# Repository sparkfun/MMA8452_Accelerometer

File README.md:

SparkFun Triple Axis Accelerometer Breakout - MMA8452Q
=============================================

<table class="table table-hover table-striped table-bordered">
  <tr align="center">
   <td></td>
   <td></td>
  </tr>
  <tr align="center">
    <td>SparkFun Triple Axis Accelerometer Breakout - MMA8452Q [<a href="https://www.sparkfun.com/products/12756">SEN-12756</a>]</td>
    <td>SparkFun Triple Axis Accelerometer Breakout - MMA8452Q (with Headers)
[<a href="https://www.sparkfun.com/products/13926">BOB-13926</a>]</td>
  </tr>
</table>

This breakout board makes it easy to use the tiny MMA8452Q accelerometer in your project. 
The MMA8452Q is a smart low-power, three-axis, capacitive micro-machined accelerometer with 12 bits of resolution.

Repository Contents
-------------------
* **/Firmware** - Example Arduino sketches for interfacing with the accelerometer
* **/Hardware** - All Eagle design files (.brd, .sch)
* **/Libraries** - Libraries for use with the accelerometer
* **/Production** - Production panel files (.brd)

Documentation
--------------
* Library
  * **[Arduino Library](https://github.com/sparkfun/SparkFun_MMA8452Q_Arduino_Library)** - Arduino library for the accelerometer.
  * **[Particle Library](https://github.com/sparkfun/SparkFun_MMA8452Q_Particle_Library)** - Particle library for the accelerometer.
* **[Hookup Guide](https://learn.sparkfun.com/tutorials/mma8452q-accelerometer-breakout-hookup-guide)** - Basic hookup guide for the accelerometer.
* **[SparkFun Fritzing repo](https://github.com/sparkfun/Fritzing_Parts)** - Fritzing diagrams for SparkFun products.
* **[SparkFun 3D Model repo](https://github.com/sparkfun/3D_Models)** - 3D models of SparkFun products. 

Product Versions
----------------
* [BOB-13926](https://www.sparkfun.com/products/13926) - Version 11 with headers
* [SEN-12756](https://www.sparkfun.com/products/12756) - Version 11
* *[SEN-10955 (Retired)](https://www.sparkfun.com/products/retired/10955)* - Version 11

License Information
-------------------
This product is _**open source**_! 

The **hardware** is released under [Creative Commons ShareAlike 4.0 International](https://creativecommons.org/licenses/by-sa/4.0/).

The **code** is beerware; if you see me (or any other SparkFun employee) at the local, and you've found our code helpful, please buy us a round!

Please use, reuse, and modify these files as you see fit. Please maintain attribution to SparkFun Electronics and release anything derivative under the same license.

Distributed as-is; no warranty is given.

- Your friends at SparkFun.

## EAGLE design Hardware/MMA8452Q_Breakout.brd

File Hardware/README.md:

SparkFun <PRODUCT NAME> Design Files
=====================================

The .sch and .brd files hare are Eagle CAD schematic and PCB design files from SparkFun Electronics.
A freeware version of Eagle can be found [here](http://www.cadsoftusa.com/download-eagle/freeware/). 

License
---------
This product is open source! 
The hardware is released under [Creative Commons ShareAlike 4.0 International](https://creativecommons.org/licenses/by-sa/4.0/).

Please use, reuse, and modify these files as you see fit. Please maintain attribution to SparkFun Electronics and release anything derivative under the same license.

Distributed as-is; no warranty is given.

- Your friends at SparkFun.

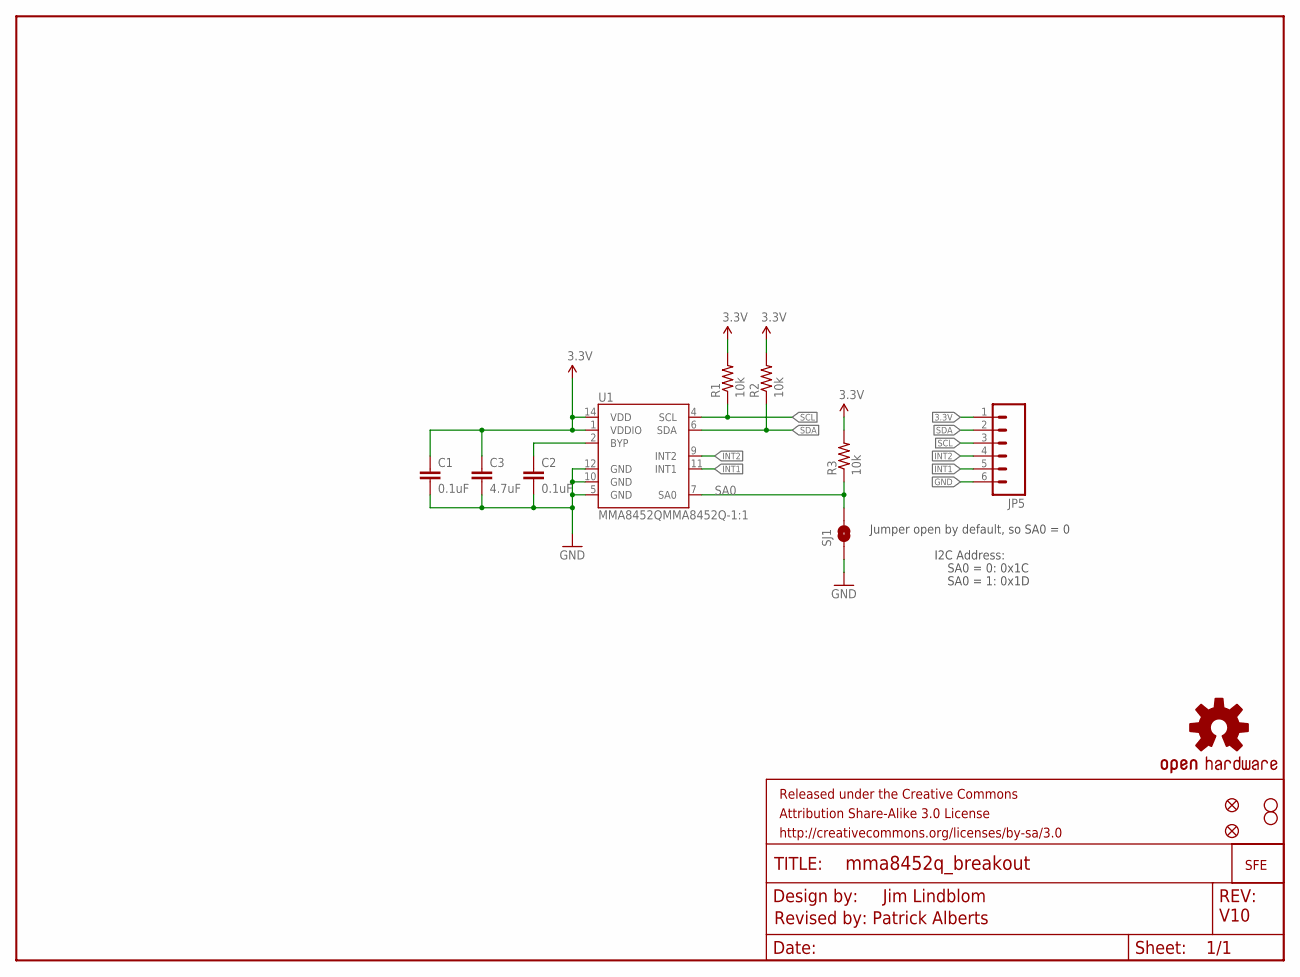
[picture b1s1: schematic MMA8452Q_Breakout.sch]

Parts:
C1, C2: 0.1uF; 0603-CAP
C3: 4.7uF; 0603-CAP
FID1, FID2: FIDUCIAL1X2; FIDUCIAL-1X2
FRAME1: FRAME-LETTER; CREATIVE_COMMONS
JP1: LOGO-SFESK; SFE-LOGO-FLAME
JP3, JP4: STAND-OFF
JP5: M06SIP; 1X06
R1, R2, R3: 10k; 0603-RES
SJ1: SOLDERJUMPERNO; SJ_2S-NO
U1: MMA8452QMMA8452Q-1:1; MMA8452Q-1:1
U$1: OSHW-LOGOS; OSHW-LOGO-S

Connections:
3.3V: C1.1, C3.1, JP5.1, R1.2, R2.2, R3.2, U1.1 (VDDIO), U1.14 (VDD)
BYP: C2.1, U1.2 (BYP)
GND: C1.2, C2.2, C3.2, JP5.6, SJ1.1, U1.5 (GND), U1.10 (GND), U1.12 (GND)
INT1: JP5.5, U1.11 (INT1)
INT2: JP5.4, U1.9 (INT2)
SA0: R3.1, SJ1.2, U1.7 (SA0)
SCL: JP5.3, R1.1, U1.4 (SCL)
SDA: JP5.2, R2.1, U1.6 (SDA)

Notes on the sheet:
Jim Lindblom
I2C Address:
SA0 = 0: 0x1C
SA0 = 1: 0x1D
Jumper open by default, so SA0 = 0
Revised by: Patrick Alberts
V10

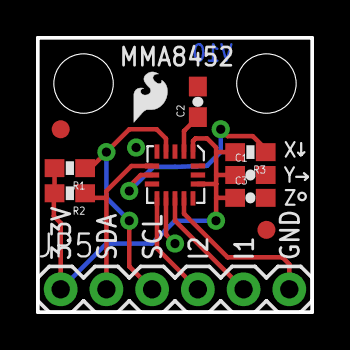
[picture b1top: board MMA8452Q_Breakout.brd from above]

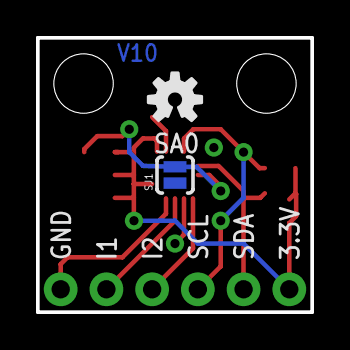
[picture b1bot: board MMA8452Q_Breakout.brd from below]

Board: 2 copper layers, 15.2 x 15.2 mm, 16 parts (2 on the bottom side), 8 nets.

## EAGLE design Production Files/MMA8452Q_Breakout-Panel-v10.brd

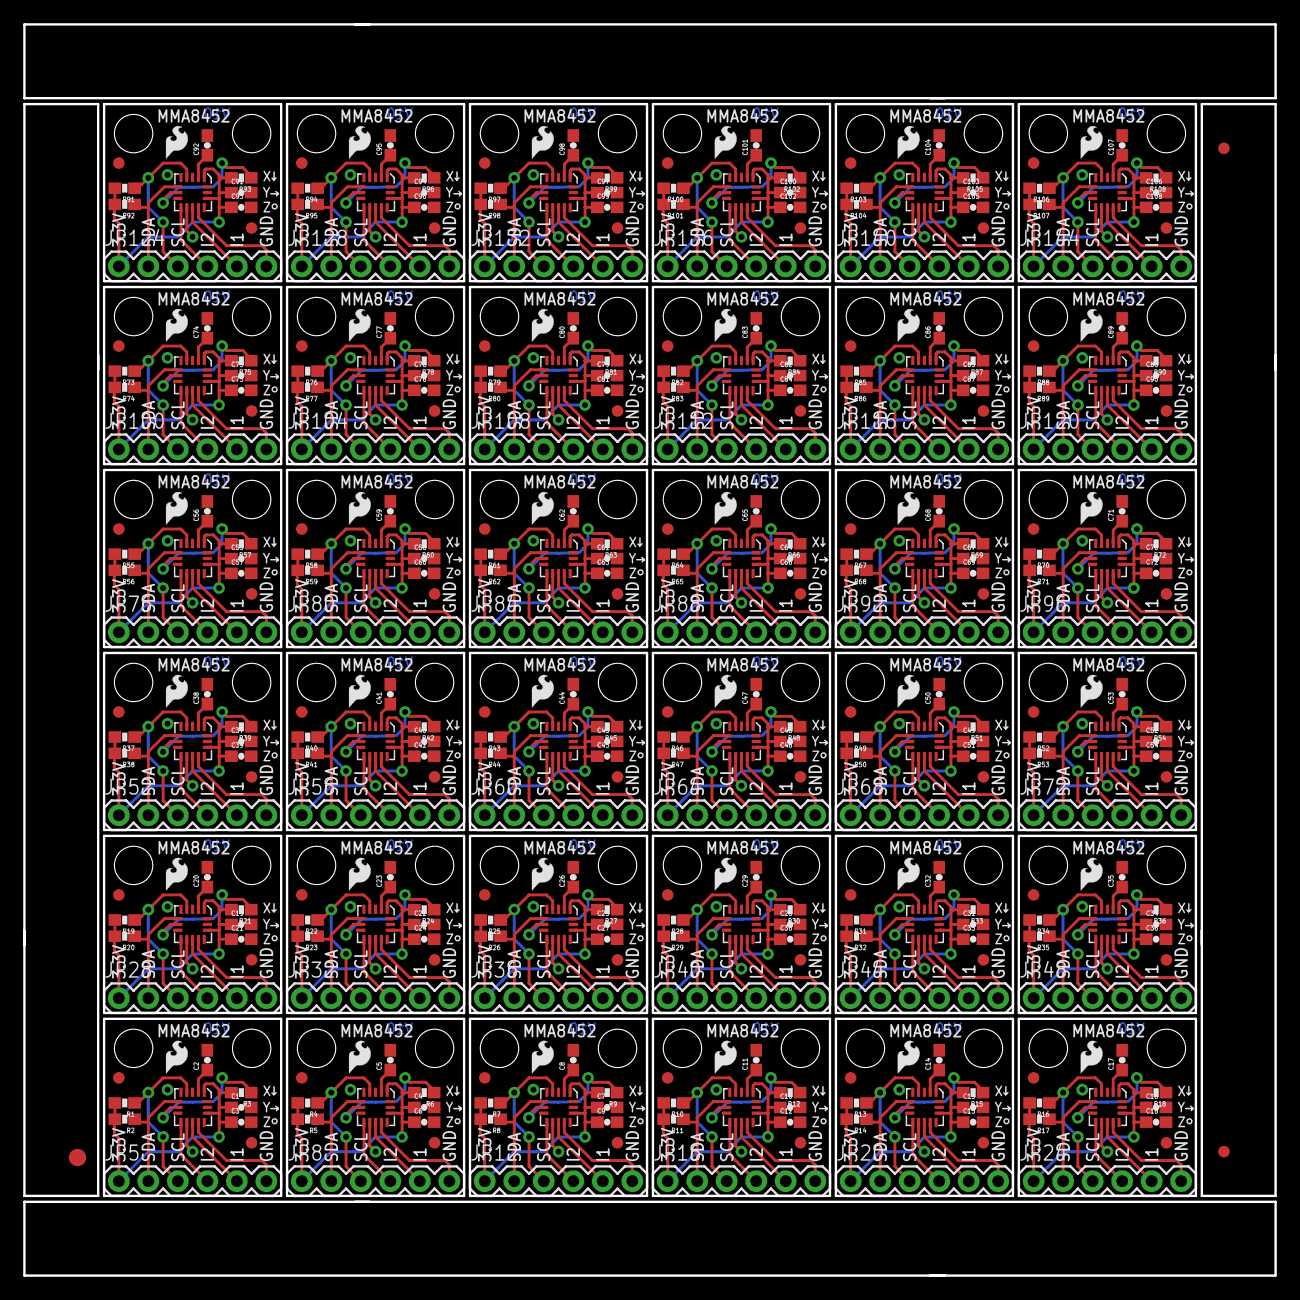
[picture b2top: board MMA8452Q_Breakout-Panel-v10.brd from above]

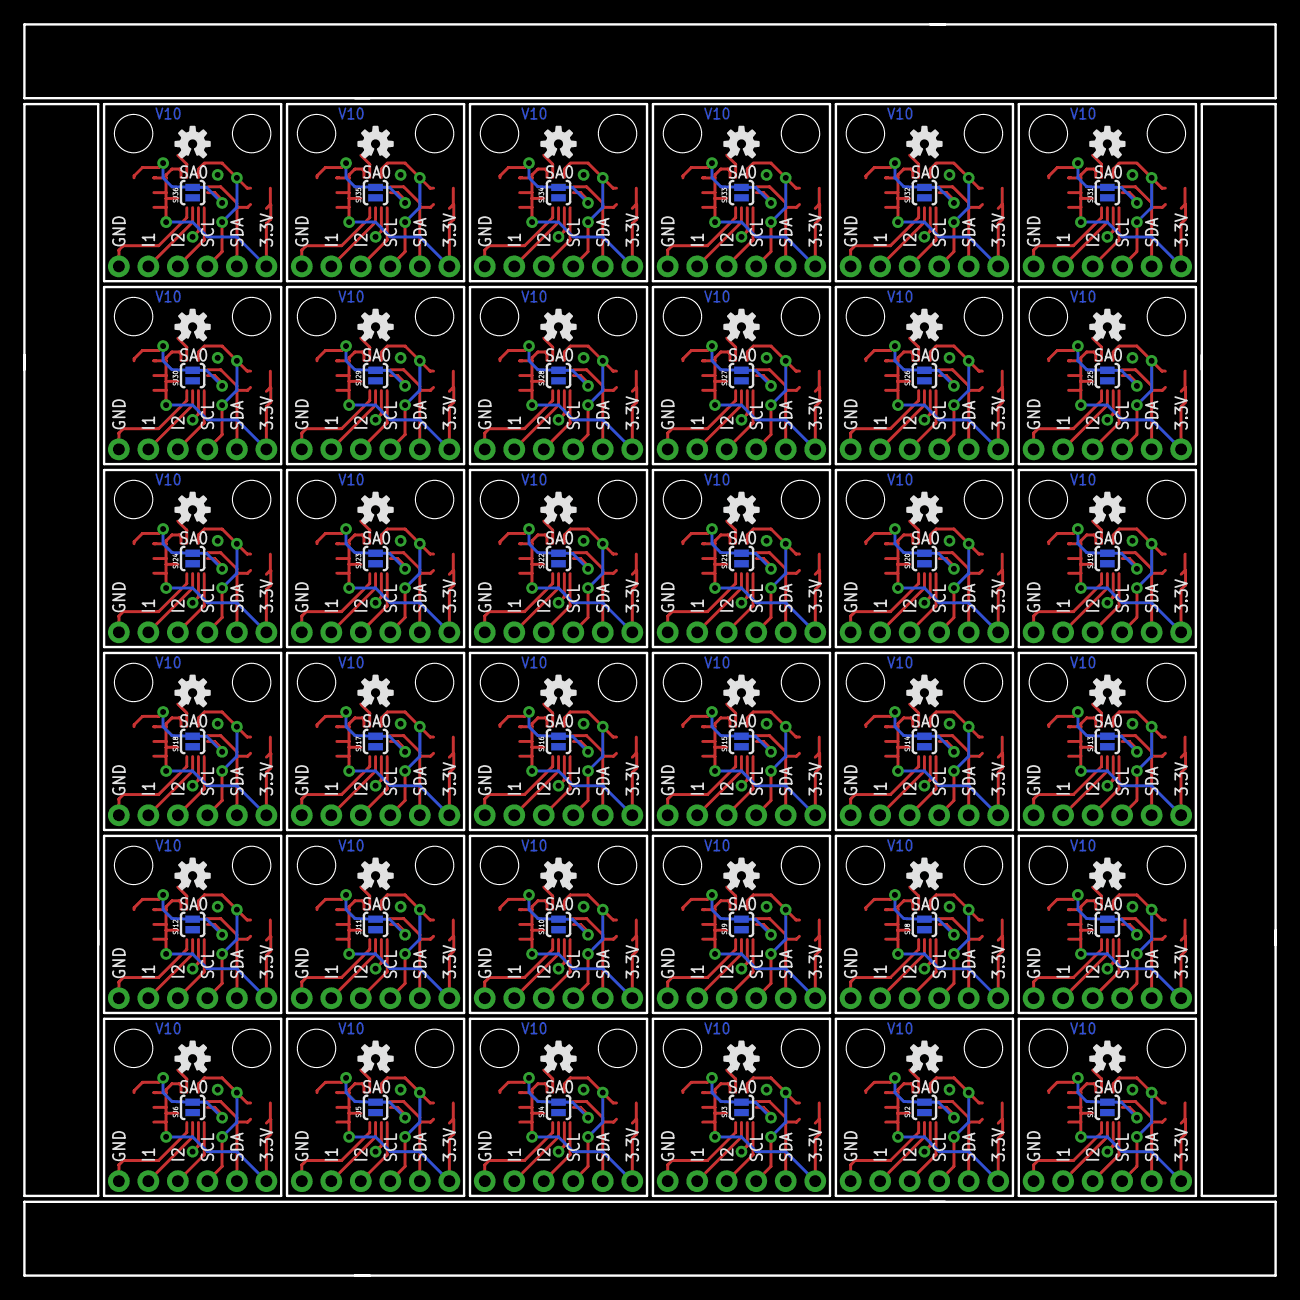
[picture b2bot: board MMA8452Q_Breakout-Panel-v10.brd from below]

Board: 2 copper layers, 107.7 x 107.7 mm, 543 parts (72 on the bottom side), 288 nets.

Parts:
C1, C2, C4, C5, C7, C8, C10, C11, C13, C14, C16, C17, C19, C20, C22, C23, C25, C26, C28, C29, C31, C32, C34, C35, C37, C38, C40, C41, C43, C44, C46, C47, C49, C50, C52, C53, C55, C56, C58, C59, C61, C62, C64, C65, C67, C68, C70, C71, C73, C74, C76, C77, C79, C80, C82, C83, C85, C86, C88, C89, C91, C92, C94, C95, C97, C98, C100, C101, C103, C104, C106, C107: 0.1uF; 0603-CAP
C3, C6, C9, C12, C15, C18, C21, C24, C27, C30, C33, C36, C39, C42, C45, C48, C51, C54, C57, C60, C63, C66, C69, C72, C75, C78, C81, C84, C87, C90, C93, C96, C99, C102, C105, C108: 4.7uF; 0603-CAP
E$1: FIDUCIAL-1.5X3
E$4, E$6: FIDUCIAL-1X2
FID1, FID2, FID3, FID4, FID5, FID6, FID7, FID8, FID9, FID10, FID11, FID12, FID13, FID14, FID15, FID16, FID17, FID18, FID19, FID20, FID21, FID22, FID23, FID24, FID25, FID26, FID27, FID28, FID29, FID30, FID31, FID32, FID33, FID34, FID35, FID36, FID37, FID38, FID39, FID40, FID41, FID42, FID43, FID44, FID45, FID46, FID47, FID48, FID49, FID50, FID51, FID52, FID53, FID54, FID55, FID56, FID57, FID58, FID59, FID60, FID61, FID62, FID63, FID64, FID65, FID66, FID67, FID68, FID69, FID70, FID71, FID72: FIDUCIAL1X2; FIDUCIAL-1X2
JP1, JP2, JP9, JP13, JP17, JP21, JP25, JP29, JP33, JP37, JP41, JP45, JP49, JP53, JP57, JP61, JP65, JP69, JP73, JP77, JP81, JP85, JP89, JP93, JP97, JP101, JP105, JP109, JP113, JP117, JP121, JP125, JP129, JP133, JP137, JP141: LOGO-SFESK; SFE-LOGO-FLAME
JP3, JP4, JP6, JP7, JP10, JP11, JP14, JP15, JP18, JP19, JP22, JP23, JP26, JP27, JP30, JP31, JP34, JP35, JP38, JP39, JP42, JP43, JP46, JP47, JP50, JP51, JP54, JP55, JP58, JP59, JP62, JP63, JP66, JP67, JP70, JP71, JP74, JP75, JP78, JP79, JP82, JP83, JP86, JP87, JP90, JP91, JP94, JP95, JP98, JP99, JP102, JP103, JP106, JP107, JP110, JP111, JP114, JP115, JP118, JP119, JP122, JP123, JP126, JP127, JP130, JP131, JP134, JP135, JP138, JP139, JP142, JP143: STAND-OFF
JP5, JP8, JP12, JP16, JP20, JP24, JP28, JP32, JP36, JP40, JP44, JP48, JP52, JP56, JP60, JP64, JP68, JP72, JP76, JP80, JP84, JP88, JP92, JP96, JP100, JP104, JP108, JP112, JP116, JP120, JP124, JP128, JP132, JP136, JP140, JP144: 1X06
R1, R2, R3, R4, R5, R6, R7, R8, R9, R10, R11, R12, R13, R14, R15, R16, R17, R18, R19, R20, R21, R22, R23, R24, R25, R26, R27, R28, R29, R30, R31, R32, R33, R34, R35, R36, R37, R38, R39, R40, R41, R42, R43, R44, R45, R46, R47, R48, R49, R50, R51, R52, R53, R54, R55, R56, R57, R58, R59, R60, R61, R62, R63, R64, R65, R66, R67, R68, R69, R70, R71, R72, R73, R74, R75, R76, R77, R78, R79, R80, R81, R82, R83, R84, R85, R86, R87, R88, R89, R90, R91, R92, R93, R94, R95, R96, R97, R98, R99, R100, R101, R102, R103, R104, R105, R106, R107, R108: 10k; 0603-RES
SJ1, SJ2, SJ3, SJ4, SJ5, SJ6, SJ7, SJ8, SJ9, SJ10, SJ11, SJ12, SJ13, SJ14, SJ15, SJ16, SJ17, SJ18, SJ19, SJ20, SJ21, SJ22, SJ23, SJ24, SJ25, SJ26, SJ27, SJ28, SJ29, SJ30, SJ31, SJ32, SJ33, SJ34, SJ35, SJ36: SJ_2S-NO
U1, U2, U3, U4, U5, U6, U7, U8, U9, U10, U11, U12, U13, U14, U15, U16, U17, U18, U19, U20, U21, U22, U23, U24, U25, U26, U27, U28, U29, U30, U31, U32, U33, U34, U35, U36: MMA8452QMMA8452Q-1:1; MMA8452Q-1:1
U$1, U$2, U$3, U$4, U$5, U$6, U$7, U$8, U$9, U$10, U$11, U$12, U$13, U$14, U$15, U$16, U$17, U$18, U$19, U$20, U$21, U$22, U$23, U$24, U$25, U$26, U$27, U$28, U$29, U$30, U$31, U$32, U$33, U$34, U$35, U$36: OSHW-LOGOS; OSHW-LOGO-S

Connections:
3.3V: C1.1, C3.1, JP5.1, R1.2, R2.2, R3.2, U1.1, U1.14
3.3V1: C4.1, C6.1, JP8.1, R4.2, R5.2, R6.2, U2.1, U2.14
3.3V2: C7.1, C9.1, JP12.1, R7.2, R8.2, R9.2, U3.1, U3.14
3.3V3: C10.1, C12.1, JP16.1, R10.2, R11.2, R12.2, U4.1, U4.14
3.3V4: C13.1, C15.1, JP20.1, R13.2, R14.2, R15.2, U5.1, U5.14
3.3V5: C16.1, C18.1, JP24.1, R16.2, R17.2, R18.2, U6.1, U6.14
3.3V6: C19.1, C21.1, JP28.1, R19.2, R20.2, R21.2, U7.1, U7.14
3.3V7: C22.1, C24.1, JP32.1, R22.2, R23.2, R24.2, U8.1, U8.14
3.3V8: C25.1, C27.1, JP36.1, R25.2, R26.2, R27.2, U9.1, U9.14
3.3V9: C28.1, C30.1, JP40.1, R28.2, R29.2, R30.2, U10.1, U10.14
3.3V10: C31.1, C33.1, JP44.1, R31.2, R32.2, R33.2, U11.1, U11.14
3.3V11: C34.1, C36.1, JP48.1, R34.2, R35.2, R36.2, U12.1, U12.14
3.3V12: C37.1, C39.1, JP52.1, R37.2, R38.2, R39.2, U13.1, U13.14
3.3V13: C40.1, C42.1, JP56.1, R40.2, R41.2, R42.2, U14.1, U14.14
3.3V14: C43.1, C45.1, JP60.1, R43.2, R44.2, R45.2, U15.1, U15.14
3.3V15: C46.1, C48.1, JP64.1, R46.2, R47.2, R48.2, U16.1, U16.14
3.3V16: C49.1, C51.1, JP68.1, R49.2, R50.2, R51.2, U17.1, U17.14
3.3V17: C52.1, C54.1, JP72.1, R52.2, R53.2, R54.2, U18.1, U18.14
3.3V18: C55.1, C57.1, JP76.1, R55.2, R56.2, R57.2, U19.1, U19.14
3.3V19: C58.1, C60.1, JP80.1, R58.2, R59.2, R60.2, U20.1, U20.14
3.3V20: C61.1, C63.1, JP84.1, R61.2, R62.2, R63.2, U21.1, U21.14
3.3V21: C64.1, C66.1, JP88.1, R64.2, R65.2, R66.2, U22.1, U22.14
3.3V22: C67.1, C69.1, JP92.1, R67.2, R68.2, R69.2, U23.1, U23.14
3.3V23: C70.1, C72.1, JP96.1, R70.2, R71.2, R72.2, U24.1, U24.14
3.3V24: C73.1, C75.1, JP100.1, R73.2, R74.2, R75.2, U25.1, U25.14
3.3V25: C76.1, C78.1, JP104.1, R76.2, R77.2, R78.2, U26.1, U26.14
3.3V26: C79.1, C81.1, JP108.1, R79.2, R80.2, R81.2, U27.1, U27.14
3.3V27: C82.1, C84.1, JP112.1, R82.2, R83.2, R84.2, U28.1, U28.14
3.3V28: C85.1, C87.1, JP116.1, R85.2, R86.2, R87.2, U29.1, U29.14
3.3V29: C88.1, C90.1, JP120.1, R88.2, R89.2, R90.2, U30.1, U30.14
3.3V30: C91.1, C93.1, JP124.1, R91.2, R92.2, R93.2, U31.1, U31.14
3.3V31: C94.1, C96.1, JP128.1, R94.2, R95.2, R96.2, U32.1, U32.14
3.3V32: C97.1, C99.1, JP132.1, R97.2, R98.2, R99.2, U33.1, U33.14
3.3V33: C100.1, C102.1, JP136.1, R100.2, R101.2, R102.2, U34.1, U34.14
3.3V34: C103.1, C105.1, JP140.1, R103.2, R104.2, R105.2, U35.1, U35.14
3.3V35: C106.1, C108.1, JP144.1, R106.2, R107.2, R108.2, U36.1, U36.14
BYP: C2.1, U1.2
BYP1: C5.1, U2.2
BYP2: C8.1, U3.2
BYP3: C11.1, U4.2
BYP4: C14.1, U5.2
BYP5: C17.1, U6.2
BYP6: C20.1, U7.2
BYP7: C23.1, U8.2
BYP8: C26.1, U9.2
BYP9: C29.1, U10.2
BYP10: C32.1, U11.2
BYP11: C35.1, U12.2
BYP12: C38.1, U13.2
BYP13: C41.1, U14.2
BYP14: C44.1, U15.2
BYP15: C47.1, U16.2
BYP16: C50.1, U17.2
BYP17: C53.1, U18.2
BYP18: C56.1, U19.2
BYP19: C59.1, U20.2
BYP20: C62.1, U21.2
BYP21: C65.1, U22.2
BYP22: C68.1, U23.2
BYP23: C71.1, U24.2
BYP24: C74.1, U25.2
BYP25: C77.1, U26.2
BYP26: C80.1, U27.2
BYP27: C83.1, U28.2
BYP28: C86.1, U29.2
BYP29: C89.1, U30.2
BYP30: C92.1, U31.2
BYP31: C95.1, U32.2
BYP32: C98.1, U33.2
BYP33: C101.1, U34.2
BYP34: C104.1, U35.2
BYP35: C107.1, U36.2
GND: C1.2, C2.2, C3.2, JP5.6, SJ1.1, U1.5, U1.10, U1.12
GND1: C4.2, C5.2, C6.2, JP8.6, SJ2.1, U2.5, U2.10, U2.12
GND2: C7.2, C8.2, C9.2, JP12.6, SJ3.1, U3.5, U3.10, U3.12
GND3: C10.2, C11.2, C12.2, JP16.6, SJ4.1, U4.5, U4.10, U4.12
GND4: C13.2, C14.2, C15.2, JP20.6, SJ5.1, U5.5, U5.10, U5.12
GND5: C16.2, C17.2, C18.2, JP24.6, SJ6.1, U6.5, U6.10, U6.12
GND6: C19.2, C20.2, C21.2, JP28.6, SJ7.1, U7.5, U7.10, U7.12
GND7: C22.2, C23.2, C24.2, JP32.6, SJ8.1, U8.5, U8.10, U8.12
GND8: C25.2, C26.2, C27.2, JP36.6, SJ9.1, U9.5, U9.10, U9.12
GND9: C28.2, C29.2, C30.2, JP40.6, SJ10.1, U10.5, U10.10, U10.12
GND10: C31.2, C32.2, C33.2, JP44.6, SJ11.1, U11.5, U11.10, U11.12
GND11: C34.2, C35.2, C36.2, JP48.6, SJ12.1, U12.5, U12.10, U12.12
GND12: C37.2, C38.2, C39.2, JP52.6, SJ13.1, U13.5, U13.10, U13.12
GND13: C40.2, C41.2, C42.2, JP56.6, SJ14.1, U14.5, U14.10, U14.12
GND14: C43.2, C44.2, C45.2, JP60.6, SJ15.1, U15.5, U15.10, U15.12
GND15: C46.2, C47.2, C48.2, JP64.6, SJ16.1, U16.5, U16.10, U16.12
GND16: C49.2, C50.2, C51.2, JP68.6, SJ17.1, U17.5, U17.10, U17.12
GND17: C52.2, C53.2, C54.2, JP72.6, SJ18.1, U18.5, U18.10, U18.12
GND18: C55.2, C56.2, C57.2, JP76.6, SJ19.1, U19.5, U19.10, U19.12
GND19: C58.2, C59.2, C60.2, JP80.6, SJ20.1, U20.5, U20.10, U20.12
GND20: C61.2, C62.2, C63.2, JP84.6, SJ21.1, U21.5, U21.10, U21.12
GND21: C64.2, C65.2, C66.2, JP88.6, SJ22.1, U22.5, U22.10, U22.12
GND22: C67.2, C68.2, C69.2, JP92.6, SJ23.1, U23.5, U23.10, U23.12
GND23: C70.2, C71.2, C72.2, JP96.6, SJ24.1, U24.5, U24.10, U24.12
GND24: C73.2, C74.2, C75.2, JP100.6, SJ25.1, U25.5, U25.10, U25.12
GND25: C76.2, C77.2, C78.2, JP104.6, SJ26.1, U26.5, U26.10, U26.12
GND26: C79.2, C80.2, C81.2, JP108.6, SJ27.1, U27.5, U27.10, U27.12
GND27: C82.2, C83.2, C84.2, JP112.6, SJ28.1, U28.5, U28.10, U28.12
GND28: C85.2, C86.2, C87.2, JP116.6, SJ29.1, U29.5, U29.10, U29.12
GND29: C88.2, C89.2, C90.2, JP120.6, SJ30.1, U30.5, U30.10, U30.12
GND30: C91.2, C92.2, C93.2, JP124.6, SJ31.1, U31.5, U31.10, U31.12
GND31: C94.2, C95.2, C96.2, JP128.6, SJ32.1, U32.5, U32.10, U32.12
GND32: C97.2, C98.2, C99.2, JP132.6, SJ33.1, U33.5, U33.10, U33.12
GND33: C100.2, C101.2, C102.2, JP136.6, SJ34.1, U34.5, U34.10, U34.12
GND34: C103.2, C104.2, C105.2, JP140.6, SJ35.1, U35.5, U35.10, U35.12
GND35: C106.2, C107.2, C108.2, JP144.6, SJ36.1, U36.5, U36.10, U36.12
INT1: JP5.5, U1.11
INT2: JP5.4, U1.9
INT3: JP8.4, U2.9
INT4: JP8.5, U2.11
INT5: JP12.4, U3.9
INT6: JP12.5, U3.11
INT7: JP16.4, U4.9
INT8: JP16.5, U4.11
INT9: JP20.4, U5.9
INT10: JP20.5, U5.11
INT11: JP24.4, U6.9
INT12: JP24.5, U6.11
INT13: JP28.4, U7.9
INT14: JP28.5, U7.11
INT15: JP32.4, U8.9
INT16: JP32.5, U8.11
INT17: JP36.4, U9.9
INT18: JP36.5, U9.11
INT19: JP40.4, U10.9
INT20: JP40.5, U10.11
INT21: JP44.4, U11.9
INT22: JP44.5, U11.11
INT23: JP48.4, U12.9
INT24: JP48.5, U12.11
INT25: JP52.4, U13.9
INT26: JP52.5, U13.11
INT27: JP56.4, U14.9
INT28: JP56.5, U14.11
INT29: JP60.4, U15.9
INT30: JP60.5, U15.11
INT31: JP64.4, U16.9
INT32: JP64.5, U16.11
INT33: JP68.4, U17.9
INT34: JP68.5, U17.11
INT35: JP72.4, U18.9
INT36: JP72.5, U18.11
INT37: JP76.4, U19.9
INT38: JP76.5, U19.11
INT39: JP80.4, U20.9
INT40: JP80.5, U20.11
INT41: JP84.4, U21.9
INT42: JP84.5, U21.11
INT43: JP88.4, U22.9
INT44: JP88.5, U22.11
INT45: JP92.4, U23.9
INT46: JP92.5, U23.11
INT47: JP96.4, U24.9
INT48: JP96.5, U24.11
INT49: JP100.4, U25.9
INT50: JP100.5, U25.11
INT51: JP104.4, U26.9
INT52: JP104.5, U26.11
INT53: JP108.4, U27.9
INT54: JP108.5, U27.11
INT55: JP112.4, U28.9
INT56: JP112.5, U28.11
INT57: JP116.4, U29.9
INT58: JP116.5, U29.11
INT59: JP120.4, U30.9
INT60: JP120.5, U30.11
INT61: JP124.4, U31.9
INT62: JP124.5, U31.11
INT63: JP128.4, U32.9
INT64: JP128.5, U32.11
INT65: JP132.4, U33.9
INT66: JP132.5, U33.11
INT67: JP136.4, U34.9
INT68: JP136.5, U34.11
INT69: JP140.4, U35.9
INT70: JP140.5, U35.11
INT71: JP144.4, U36.9
INT72: JP144.5, U36.11
SA0: R3.1, SJ1.2, U1.7
SA1: R6.1, SJ2.2, U2.7
SA2: R9.1, SJ3.2, U3.7
SA3: R12.1, SJ4.2, U4.7
SA4: R15.1, SJ5.2, U5.7
SA5: R18.1, SJ6.2, U6.7
SA6: R21.1, SJ7.2, U7.7
SA7: R24.1, SJ8.2, U8.7
SA8: R27.1, SJ9.2, U9.7
SA9: R30.1, SJ10.2, U10.7
SA10: R33.1, SJ11.2, U11.7
SA11: R36.1, SJ12.2, U12.7
SA12: R39.1, SJ13.2, U13.7
SA13: R42.1, SJ14.2, U14.7
SA14: R45.1, SJ15.2, U15.7
SA15: R48.1, SJ16.2, U16.7
SA16: R51.1, SJ17.2, U17.7
SA17: R54.1, SJ18.2, U18.7
SA18: R57.1, SJ19.2, U19.7
SA19: R60.1, SJ20.2, U20.7
SA20: R63.1, SJ21.2, U21.7
SA21: R66.1, SJ22.2, U22.7
SA22: R69.1, SJ23.2, U23.7
SA23: R72.1, SJ24.2, U24.7
SA24: R75.1, SJ25.2, U25.7
SA25: R78.1, SJ26.2, U26.7
SA26: R81.1, SJ27.2, U27.7
SA27: R84.1, SJ28.2, U28.7
SA28: R87.1, SJ29.2, U29.7
SA29: R90.1, SJ30.2, U30.7
SA30: R93.1, SJ31.2, U31.7
SA31: R96.1, SJ32.2, U32.7
SA32: R99.1, SJ33.2, U33.7
SA33: R102.1, SJ34.2, U34.7
SA34: R105.1, SJ35.2, U35.7
SA35: R108.1, SJ36.2, U36.7
SCL: JP5.3, R1.1, U1.4
SCL1: JP8.3, R4.1, U2.4
SCL2: JP12.3, R7.1, U3.4
SCL3: JP16.3, R10.1, U4.4
SCL4: JP20.3, R13.1, U5.4
SCL5: JP24.3, R16.1, U6.4
SCL6: JP28.3, R19.1, U7.4
SCL7: JP32.3, R22.1, U8.4
SCL8: JP36.3, R25.1, U9.4
SCL9: JP40.3, R28.1, U10.4
SCL10: JP44.3, R31.1, U11.4
SCL11: JP48.3, R34.1, U12.4
SCL12: JP52.3, R37.1, U13.4
SCL13: JP56.3, R40.1, U14.4
SCL14: JP60.3, R43.1, U15.4
SCL15: JP64.3, R46.1, U16.4
SCL16: JP68.3, R49.1, U17.4
SCL17: JP72.3, R52.1, U18.4
SCL18: JP76.3, R55.1, U19.4
SCL19: JP80.3, R58.1, U20.4
SCL20: JP84.3, R61.1, U21.4
SCL21: JP88.3, R64.1, U22.4
SCL22: JP92.3, R67.1, U23.4
SCL23: JP96.3, R70.1, U24.4
SCL24: JP100.3, R73.1, U25.4
SCL25: JP104.3, R76.1, U26.4
SCL26: JP108.3, R79.1, U27.4
SCL27: JP112.3, R82.1, U28.4
SCL28: JP116.3, R85.1, U29.4
SCL29: JP120.3, R88.1, U30.4
SCL30: JP124.3, R91.1, U31.4
SCL31: JP128.3, R94.1, U32.4
SCL32: JP132.3, R97.1, U33.4
SCL33: JP136.3, R100.1, U34.4
SCL34: JP140.3, R103.1, U35.4
SCL35: JP144.3, R106.1, U36.4
SDA: JP5.2, R2.1, U1.6
SDA1: JP8.2, R5.1, U2.6
SDA2: JP12.2, R8.1, U3.6
SDA3: JP16.2, R11.1, U4.6
SDA4: JP20.2, R14.1, U5.6
SDA5: JP24.2, R17.1, U6.6
SDA6: JP28.2, R20.1, U7.6
SDA7: JP32.2, R23.1, U8.6
SDA8: JP36.2, R26.1, U9.6
SDA9: JP40.2, R29.1, U10.6
SDA10: JP44.2, R32.1, U11.6
SDA11: JP48.2, R35.1, U12.6
SDA12: JP52.2, R38.1, U13.6
SDA13: JP56.2, R41.1, U14.6
SDA14: JP60.2, R44.1, U15.6
SDA15: JP64.2, R47.1, U16.6
SDA16: JP68.2, R50.1, U17.6
SDA17: JP72.2, R53.1, U18.6
SDA18: JP76.2, R56.1, U19.6
SDA19: JP80.2, R59.1, U20.6
SDA20: JP84.2, R62.1, U21.6
SDA21: JP88.2, R65.1, U22.6
SDA22: JP92.2, R68.1, U23.6
SDA23: JP96.2, R71.1, U24.6
SDA24: JP100.2, R74.1, U25.6
SDA25: JP104.2, R77.1, U26.6
SDA26: JP108.2, R80.1, U27.6
SDA27: JP112.2, R83.1, U28.6
SDA28: JP116.2, R86.1, U29.6
SDA29: JP120.2, R89.1, U30.6
SDA30: JP124.2, R92.1, U31.6
SDA31: JP128.2, R95.1, U32.6
SDA32: JP132.2, R98.1, U33.6
SDA33: JP136.2, R101.1, U34.6
SDA34: JP140.2, R104.1, U35.6
SDA35: JP144.2, R107.1, U36.6

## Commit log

2012-11-06 Original commit of example sketch.
2012-11-06 Very basic whitespace corrections.
    Replaced many /* */ with //. A few tab and space corrections.
2012-11-07 Created a basic example of how to read X/Y/Z using Wire.h library
    Jim's code is very good and shows many features of the MMA8452. I wanted
    a basic sketch that just gave me X/Y/Z.
2012-11-07 Adding in Jim's Eagle files.
2013-03-07 adding readme, seeding with standard information
2013-04-22 Cleaning up repo structure.
2013-04-22 Updated README for new repo structure.
2013-08-09 Update README.md
    Fixing product link to the correct page.
2014-02-14 0402-0603/1:1/schematic changes
    0603 update, 1:1 on the MMAQ and Schematic changes
2014-03-06 added board fiducials
2014-03-06 Created Panel v10
2014-04-16 Fix code for handling sign extension of negative 12-bit values. Previous code was incorrect; this code is also faster and simpler
2014-06-03 Adding MMA8452Q Arduino library. FW reorganize
    Adding a simple MMA8452Q Arduino library.
    Moving older, stand-alone sketches to a new folder.
2014-06-09 Added Fritzing part
2014-11-23 Negative numbers display fix
2015-05-14 Adding library files from product repo, updating to Arduino 1.6.4 format
2015-05-14 Updating READMEs, file directory structure
2015-05-14 Squashed 'Libraries/Arduino/' content from commit 0b06355
    git-subtree-dir: Libraries/Arduino
    git-subtree-split: 0b06355de12e4993e16d56b6a62ae393aa4d2225
2015-05-14 Removing fritzing parts to Fritzing repo
2015-05-14 Updating version number in schematic
2015-06-16 Fixing I2C address on schematic
2016-01-21 Renaming MMA8452Q status register reference to STATUS_MMA8452Q
2016-01-21 Fixing ODR masking bits.
2016-01-21 Updating version number.
2016-03-09 Squashed 'Libraries/Arduino/' changes from 0b06355..3e911ea
    3e911ea Updating library version number to 1.2.0 to stay in sync across repos
    2e3ad8b @PlatformIO Library Registry manifest file
    d8e6527 Fixing ODR masking bits.
    6a4f30b Renaming MMA8452Q status register reference to STATUS_MMA8452Q
    git-subtree-dir: Libraries/Arduino
    git-subtree-split: 3e911eac8cf2ec890e51db660657a7c575e82b9e
2018-03-22 Squashed 'Libraries/Arduino/' changes from 3e911ea..7a68c33
    7a68c33 Merge pull request #6 from overlord1123/master
    6eb0cef Merge branch 'hang-fix' as it offers a better result.
    2216189 Fixed hang when the number of bytes cannot be read due to an error.
    c261378 Alinged the register entries of MMA8452Q_Register
    d5e1ad6 Added timeout functionality for Wire transmission
    git-subtree-dir: Libraries/Arduino
2018-04-02 Update README.md
    link breakout board with headers and product versions.
2019-05-01 Removing old libraries. Adding links to formal libs in readme.
2019-05-01 Removing old firmware. Much better examples are included in the library.

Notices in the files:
parts and their libraries:
SparkFun-Sensors: Licensing: CC v3.0 Share-Alike You are welcome to use this library for commercial purposes.
SparkFun-Aesthetics: Released under the Creative Commons Attribution Share-Alike 3.0 License
SparkFun-Aesthetics: http://creativecommons.org/licenses/by-sa/3.0
